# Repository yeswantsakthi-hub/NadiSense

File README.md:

# NadiSense — continuous-wear smart ring for overnight pulse-based screening

**Vishwakarma Awards 2026-27 · Frontier Diagnostics: The Next Vital Signs · Application ID VK26-AU-FD-0015**
Rajalakshmi Engineering College, Chennai · Team: Ring of Care · Faculty guide: Dr. L. Bhagyalakshmi, Professor, Dept. of ECE

NadiSense turns Nadi Pariksha — the traditional reading of the pulse's rate, rhythm, force and hardness — into
measurable photoplethysmography (PPG) features. A finger-worn ring records the pulse wave, SpO₂, skin temperature
and motion through the night and flags risk for:

- **AF-type irregular rhythm** (beat-to-beat interval variability)
- **Sleep-apnea risk** (overnight SpO₂ desaturation events)
- **Hypertension risk trends** (PPG stiffness index — Kathinya)
- **Baseline deviation** (heart rate, temperature)

It screens and refers to a clinician; it does not diagnose or report blood-pressure numbers.

## Repository layout

| Folder | Contents |
|---|---|
| `cad/` | Parametric ring model (`nadisense_ring.py`, CadQuery), full assembly `NadiSense_Ring_v2.step`, shell `Outer_shell.step`, one STL per part, render script |
| `fea/` | Linear-static FEA of the shell (`fea_squeeze.py`), results for three meshes (`fea_results.jsonl`), stress plot |
| `electronics/kicad/` | (Stage 2 submission, simplified) KiCad 7 project: wired schematic, project symbol library, ERC report (0 errors, 0 warnings), netlist, PDF and PNG of the sheet, generator script |
| `electronics/ring_v2_revB/` | **Rev B schematic + flex PCB**: manufacturer pin maps, routed 2-layer flex, DRC 0 errors / 0 unconnected, Gerbers, BOM, pick-and-place, renders |
| `electronics/` | Power budget (`power_budget.py` + results) |
| `renders/` | Assembled, half-section and exploded views |
| `docs/` | Design summary, Stage 2 deck PDF, FreeCAD and KiCad screenshots |
| `app/` | Companion app (React + Vite + Firebase), live at https://nadisense-app.vercel.app, runs on simulated sensor data until the ring is built |

## Key design numbers

| Item | Value | Source |
|---|---|---|
| Ring envelope | ID 19 mm, OD 26 mm, width 8 mm | `cad/nadisense_ring.py` |
| Battery | 12 mAh curved Li-Po (245 mm³ cavity) | CAD volume |
| Average current | 40 µA (night 98 µA, day 12 µA) | `electronics/power_budget.py` |
| Battery life | 9.9 days nominal, 6.0 days worst case | `electronics/power_budget.py` |
| Shell FEA, 50 N squeeze | Peak von Mises 8.5 MPa, deflection 0.12 mm, FoS 5.9 | `fea/fea_results.jsonl` |
| Mesh convergence | 9.35 → 8.53 → 8.46 MPa (0.8 % last step) | `fea/fea_results.jsonl` |
| Unit BOM (estimate) | ₹4,370 | `docs/design_summary.md` |

## Reproduce

```bash
pip install cadquery pyvista tetgen scikit-fem pyamg kiutils matplotlib
python cad/nadisense_ring.py cad/            # STEP + STL
python cad/render_pv.py cad/ renders/         # renders
python fea/fea_squeeze.py cad/ fea/ 0.08 0.5 pq2.0Q plot   # FEA (about 4 min, about 3 GB RAM)
python electronics/power_budget.py           # power budget
python electronics/kicad/kicad_gen.py electronics/kicad/   # KiCad schematic (needs KiCad 7 symbol libraries)
```

## Hardware

nRF52840 (BLE 5 SoC) · MAX86141 optical AFE with red 660 nm / IR 880 nm LEDs and Si photodiode · TMP117 (±0.1 °C) ·
LIS2DW12 accelerometer · BQ25120A charger with 2.2 µH buck inductor (3.3 V SYS) · 12 mAh Li-Po · biocompatible SLA resin shell with clear optical window.

Renders, the schematic image and the FEA plot were generated with AI assistance from these design files.

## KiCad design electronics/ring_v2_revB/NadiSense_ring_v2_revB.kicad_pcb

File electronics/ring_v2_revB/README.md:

# NadiSense ring v2 - schematic + flex PCB, Rev B

Rev B replaces the Stage 2 simplified schematic (`../kicad/`) and the Rev A layout study. Every IC now uses its
manufacturer pin / ball map and the support parts its data sheet calls for, and the flex PCB is routed against
those real footprints.

| Item | Rev B |
|---|---|
| Board | 66.8 x 6.0 mm strip, wraps 330 deg at r = 11.6 mm inside the ring; optics centred at 24.3 mm under the window |
| Stackup | 2-layer polyimide flex: 25 um PI, 12 um Cu + plating, 25 um coverlay both sides, ENIG, ~0.11 mm |
| Vias | 77 laser vias 0.2/0.1 mm in the BGA pads (filled + capped, VIPPO); 265 routing / ground-stitching vias 0.35/0.15 mm |
| Rules | 75 um track / 75 um space, 0.15 mm copper-to-edge, 0.2 mm hole-to-hole |
| Pours | GND top (solid); bottom solid under the stiffened IC sections, cross-hatched in the bend sections |
| Parts | 43 on the top (finger) side, 6 test pads on the bottom; 49 total, 37 nets |
| Checks | KiCad 7.0.11 DRC **0 violations, 0 unconnected** (`DRC.rpt`); board pads vs schematic **0 mismatches** (`verify_pcb.py`); schematic netlist vs design **0 problems** (`verify_net.py`) |

## Power architecture (changed from Stage 2)

The BQ25120A buck output (SYS) is the single **1.8 V rail** for every IC. The nRF52840 runs in normal-voltage
mode (VDD = VDDH = 1.8 V, internal LDOs), so no 3.3 V rail is needed. The LEDs run from VBAT through the
MAX86141 drivers. The Stage 2 deck and report describe a 3.3 V buck feeding the nRF52840 regulator; Rev B
simplifies this.

## Parts and pin maps

| Ref | Part | Package / footprint | Pin-map source |
|---|---|---|---|
| U1 | nRF52840-CKAA | WLCSP-94, 0.35 mm pitch | Nordic nRF52840 PS, "Pin assignments - WLCSP" |
| U2 | MAX86141ENP+ | WLP-20 (5 x 4), 0.4 mm | ADI MAX86140/86141 data sheet, bump configuration |
| U3 | TMP117AIDRVR | WSON-6 2 x 2 mm + pad | TI TMP117 data sheet, pin functions |
| U4 | LIS2DW12TR | LGA-12 2 x 2 mm | ST LIS2DW12 data sheet, pin description |
| U5 | BQ25120AYFPR | DSBGA-25 (5 x 5), 0.5 mm | TI BQ25120A data sheet, pin configuration |

nRF52840 signal map: SPI SCK C10 (P0.04), MOSI D10 (P0.05), MISO E10 (P0.08), AFE_CS F10 (P1.09), AFE_INT G10
(P0.12); I2C SDA B10 (P0.01), SCL K7 (P0.15); ACC_INT A6 (P0.28), TEMP_ALRT K3 (P0.22), CHG_INT K2 (P0.25),
CHG_CD A7 (P0.30); nRESET K6; SWD J2/H2. Unused P0.29 (C7) is tied to GND to link the fenced-in VSS ball B7.
I2C addresses: TMP117 0x48, LIS2DW12 0x18, BQ25120A 0x6A.

## Layout, left to right

Chip antenna AE1 (copper keep-out) - pi-match C8/L2/C9 and 32 MHz crystal Y1 - nRF52840 U1 with decoupling -
LIS2DW12 U4 + I2C pull-ups - red LED D1, photodiode D3, IR LED D2 (optical window) - MAX86141 U2 - TMP117 U3 -
BQ25120A U5 with L1 and its capacitors / set resistors - charge pads J1 - Li-Po tabs BT1 - free strip behind the cell.
Bottom side: programming pads TP1 SWDIO, TP2 SWDCLK, TP3 nRESET, TP4 +1V8, TP5 GND next to the SoC (needs a
cut-out in the stiffener) and TP6 MR by the charger.

## Files

| File | What it is |
|---|---|
| `NadiSense_ring_v2_revB.kicad_sch` / `.kicad_pcb` / `.kicad_pro` | KiCad 7 project (open the `.kicad_pro`) |
| `NadiSense.kicad_sym`, `NadiSense.pretty/` | project symbols and footprints (IC land patterns, test pads, contacts) |
| `NadiSense_ring_v2_revB_schematic.pdf` | schematic |
| `NadiSense_ring_v2_revB_top.pdf`, `_bottom.pdf` | layer plots with the board outline and stiffeners |
| `NadiSense_ring_v2_revB_gerbers.zip`, `fab/` | Gerbers, Excellon drill + maps, pick-and-place, BOM |
| `images/` | overview, 3D flat + ring renders, routing view, assembly drawings, layer views |
| `DRC.rpt` | final design-rule check |
| `design.py` | single source of truth: parts, values, footprints, pin maps, nets |

## How the board was built

1. `build_sch.py` writes the schematic from `design.py`; `kicad-cli sch export netlist`; `verify_net.py` checks it.
2. `build_pcb.py` writes the footprints, outline, rules, rule areas, placement and via-in-pad fan-out, and a Specctra DSN.
3. Freerouting 1.9.0 routes the DSN (`-mp 120`); `route_import.py --no-pour` imports the session.
4. `finish2.py` (two-layer A* router) completes nets the autorouter left open; autorouted GND tracks are removed
   because the pours carry ground.
5. `finalize.py` adds the pours and stitching vias; `gnd_ties.py` and `gnd_bridge.py` tie the inner BGA ground and
   any isolated pour island into the main ground; `setrules.py` keeps the flex rules in the project file.
6. `drc.py`, `verify_pcb.py` for the checks; `make_outputs.py`, `drawings.py`, `render3d.py` for the deliverables.

## Before fabrication (open items)

1. **Land patterns to confirm against the package drawings:** U1 against Nordic PS section 7.2.3 (0.35 mm pitch
   derived from the 3.544 x 3.607 mm body and 10 x 10 grid), U2 against ADI outline 21-100134 / AN1891, U4 pad-1
   orientation against ST's land pattern.
2. **Fab capability:** 0.35 mm-pitch WLCSP on flex needs laser via-in-pad (filled, capped) and 75 um lines; confirm
   with the flex vendor, or move to a 4-layer flex if they prefer.
3. **Values still to set:** R4 (ISET) and R5 (IPRETERM) per TI's equations (charge current is also set over I2C);
   C8/L2/C9 antenna match to be tuned on a VNA in the potted ring; nRF52840 decoupling values (C1 DEC1 100 nF, C2
   DEC4 1 uF, C3 DEC6 47 nF, C4/C5 VDD) to be checked against Nordic's CKAA reference circuit.
4. **Antenna:** it sits next to the cell end; check range in the finished ring.
5. **Not yet done:** signal-integrity/RF simulation, thermal check of the LED drive, and a review in the KiCad GUI.

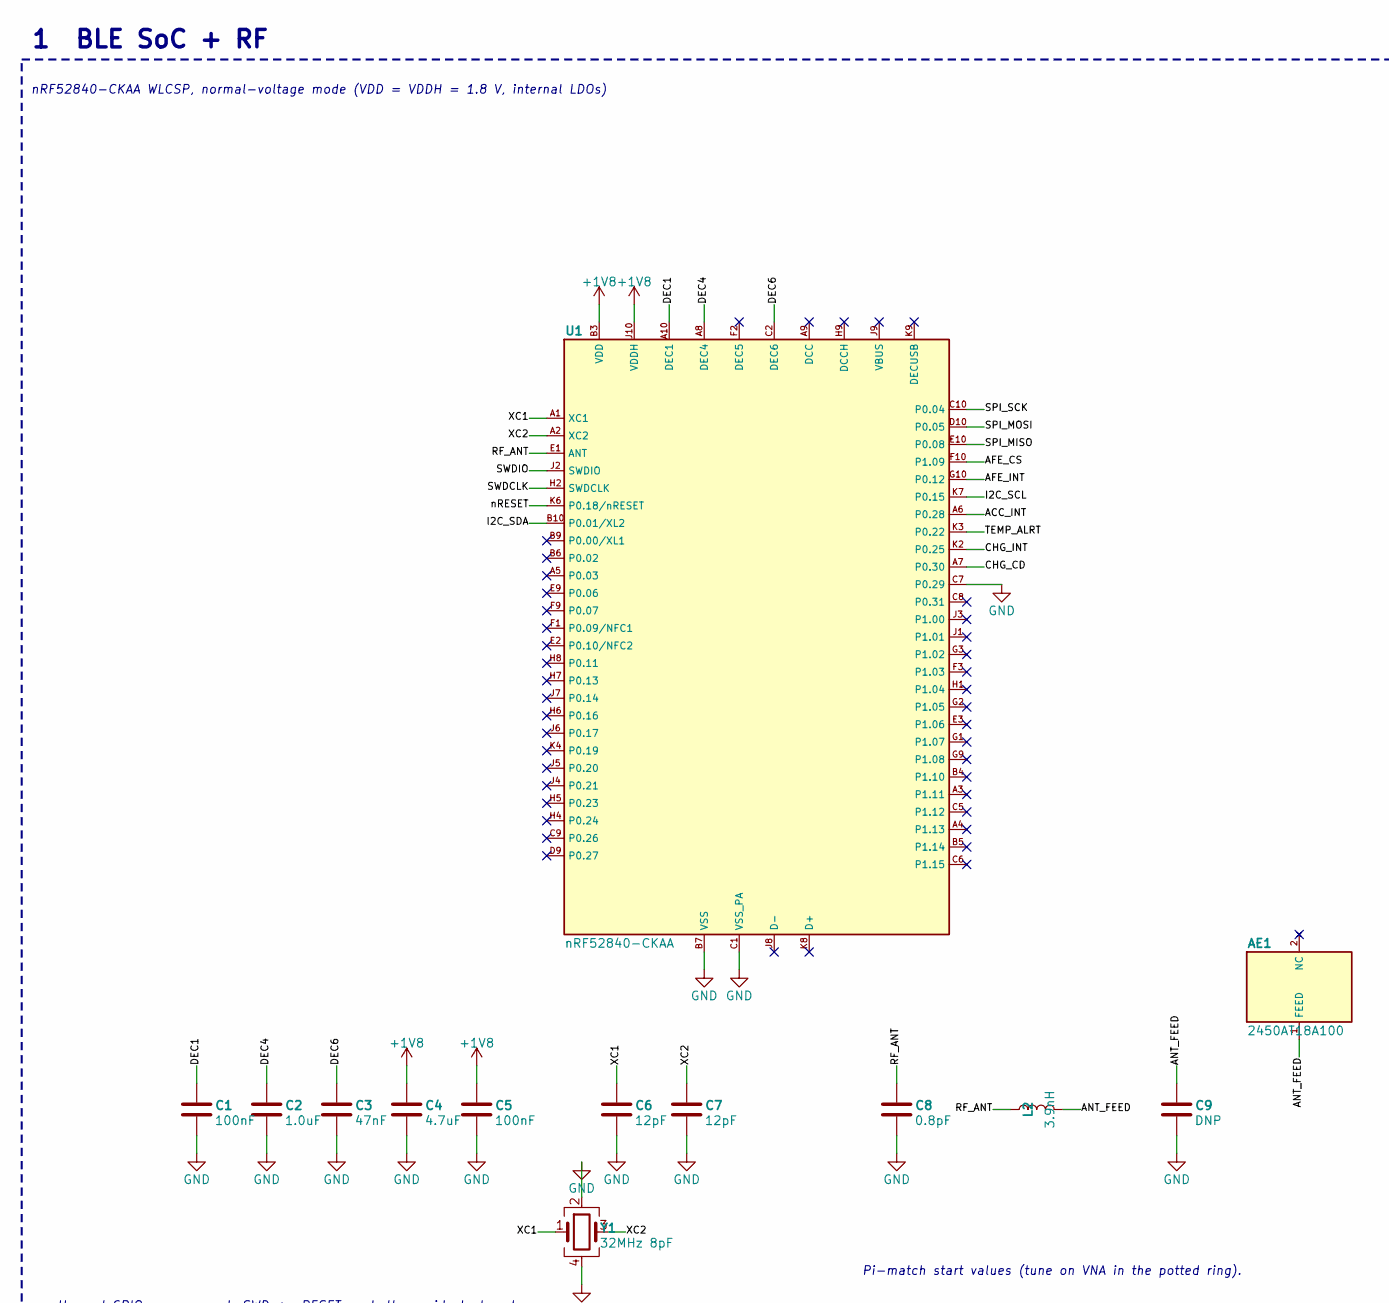
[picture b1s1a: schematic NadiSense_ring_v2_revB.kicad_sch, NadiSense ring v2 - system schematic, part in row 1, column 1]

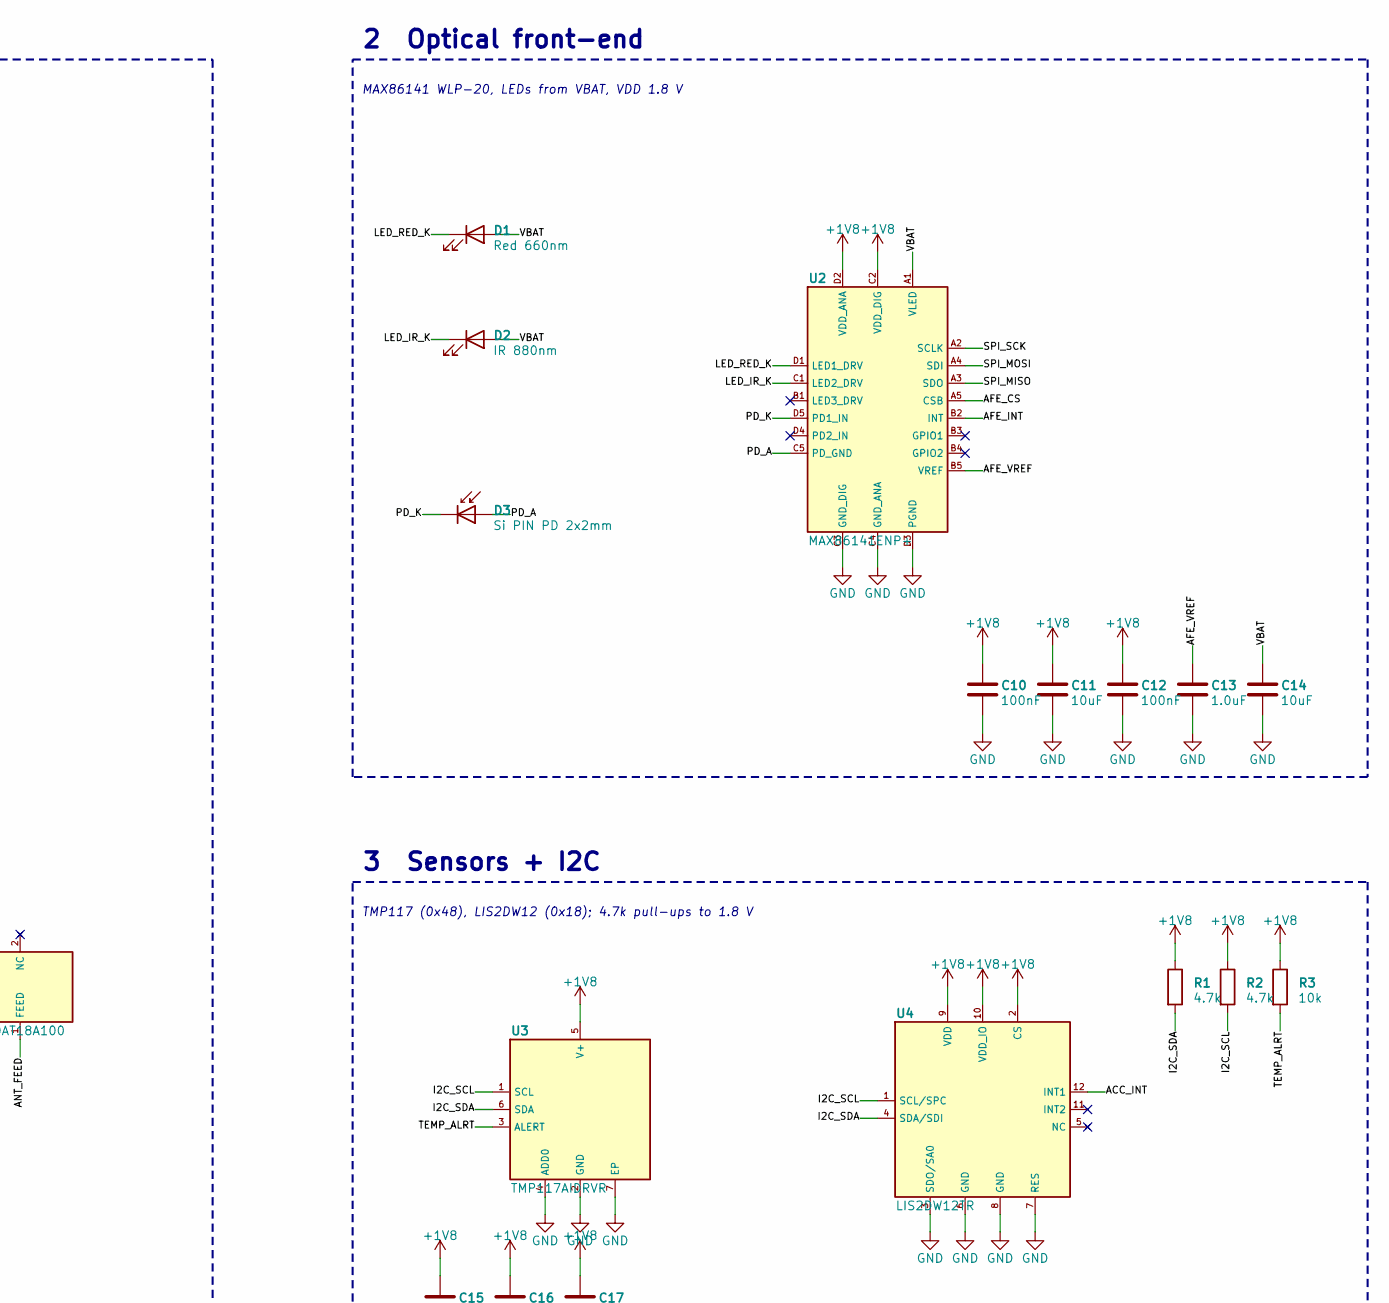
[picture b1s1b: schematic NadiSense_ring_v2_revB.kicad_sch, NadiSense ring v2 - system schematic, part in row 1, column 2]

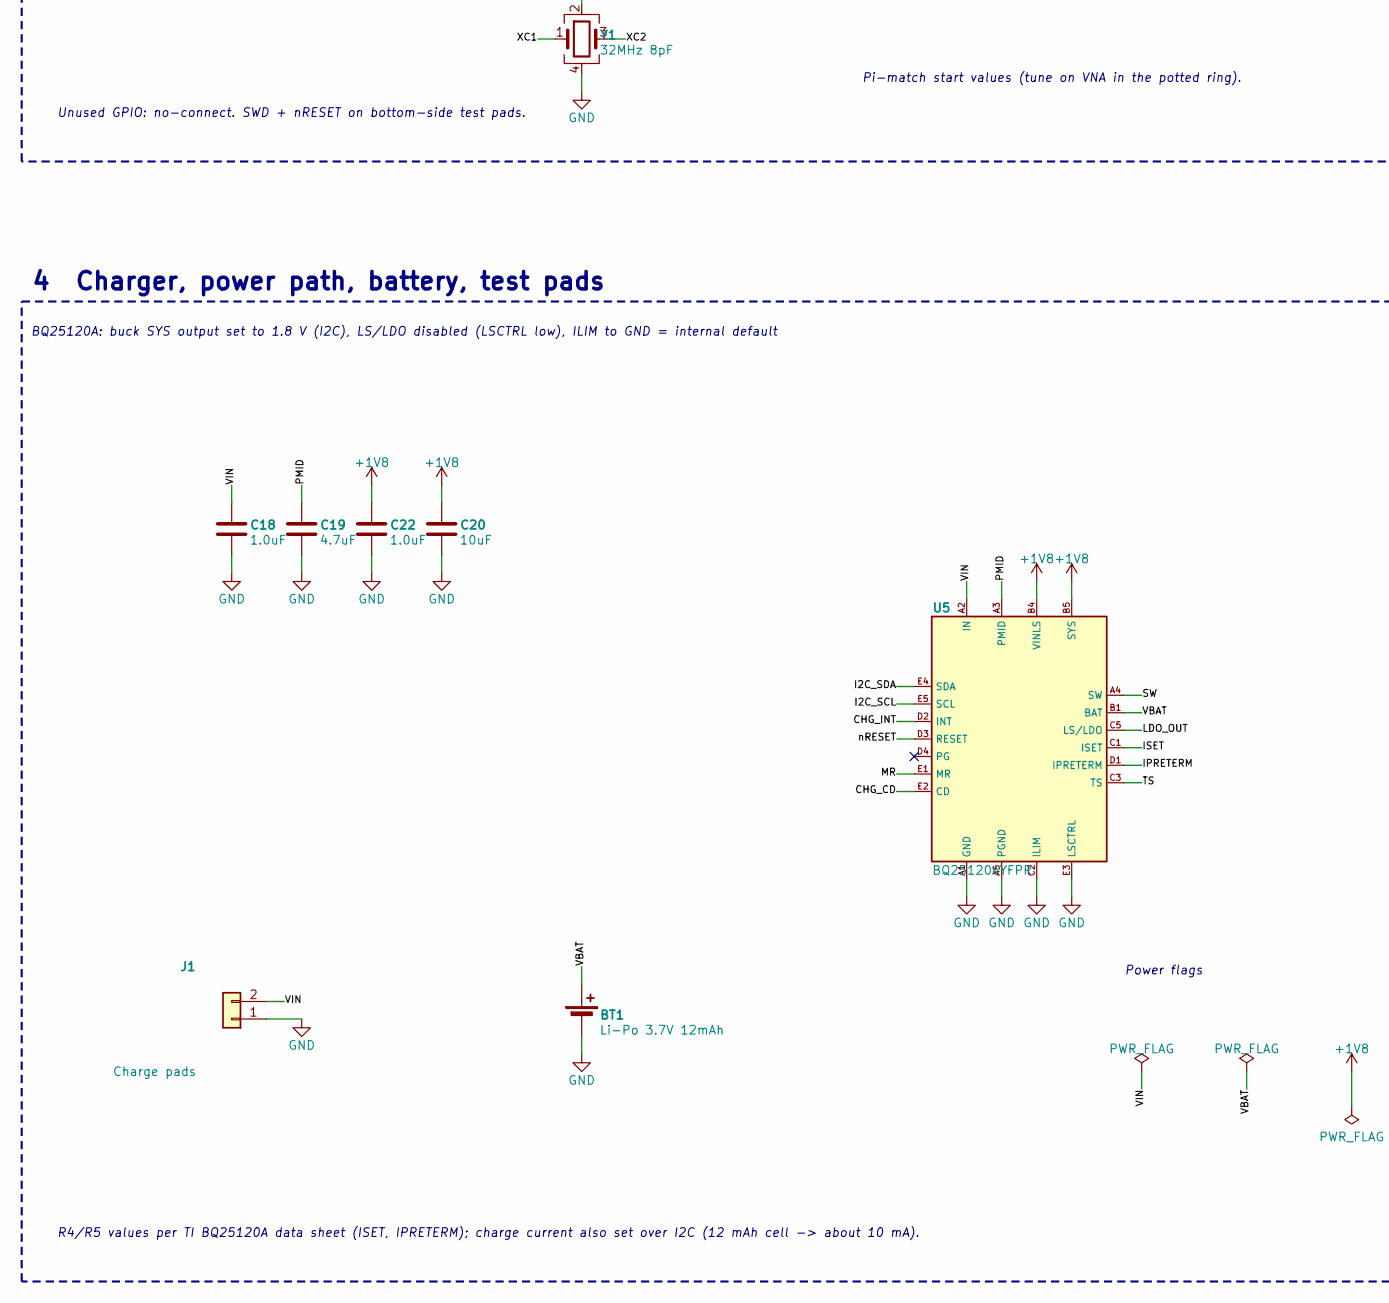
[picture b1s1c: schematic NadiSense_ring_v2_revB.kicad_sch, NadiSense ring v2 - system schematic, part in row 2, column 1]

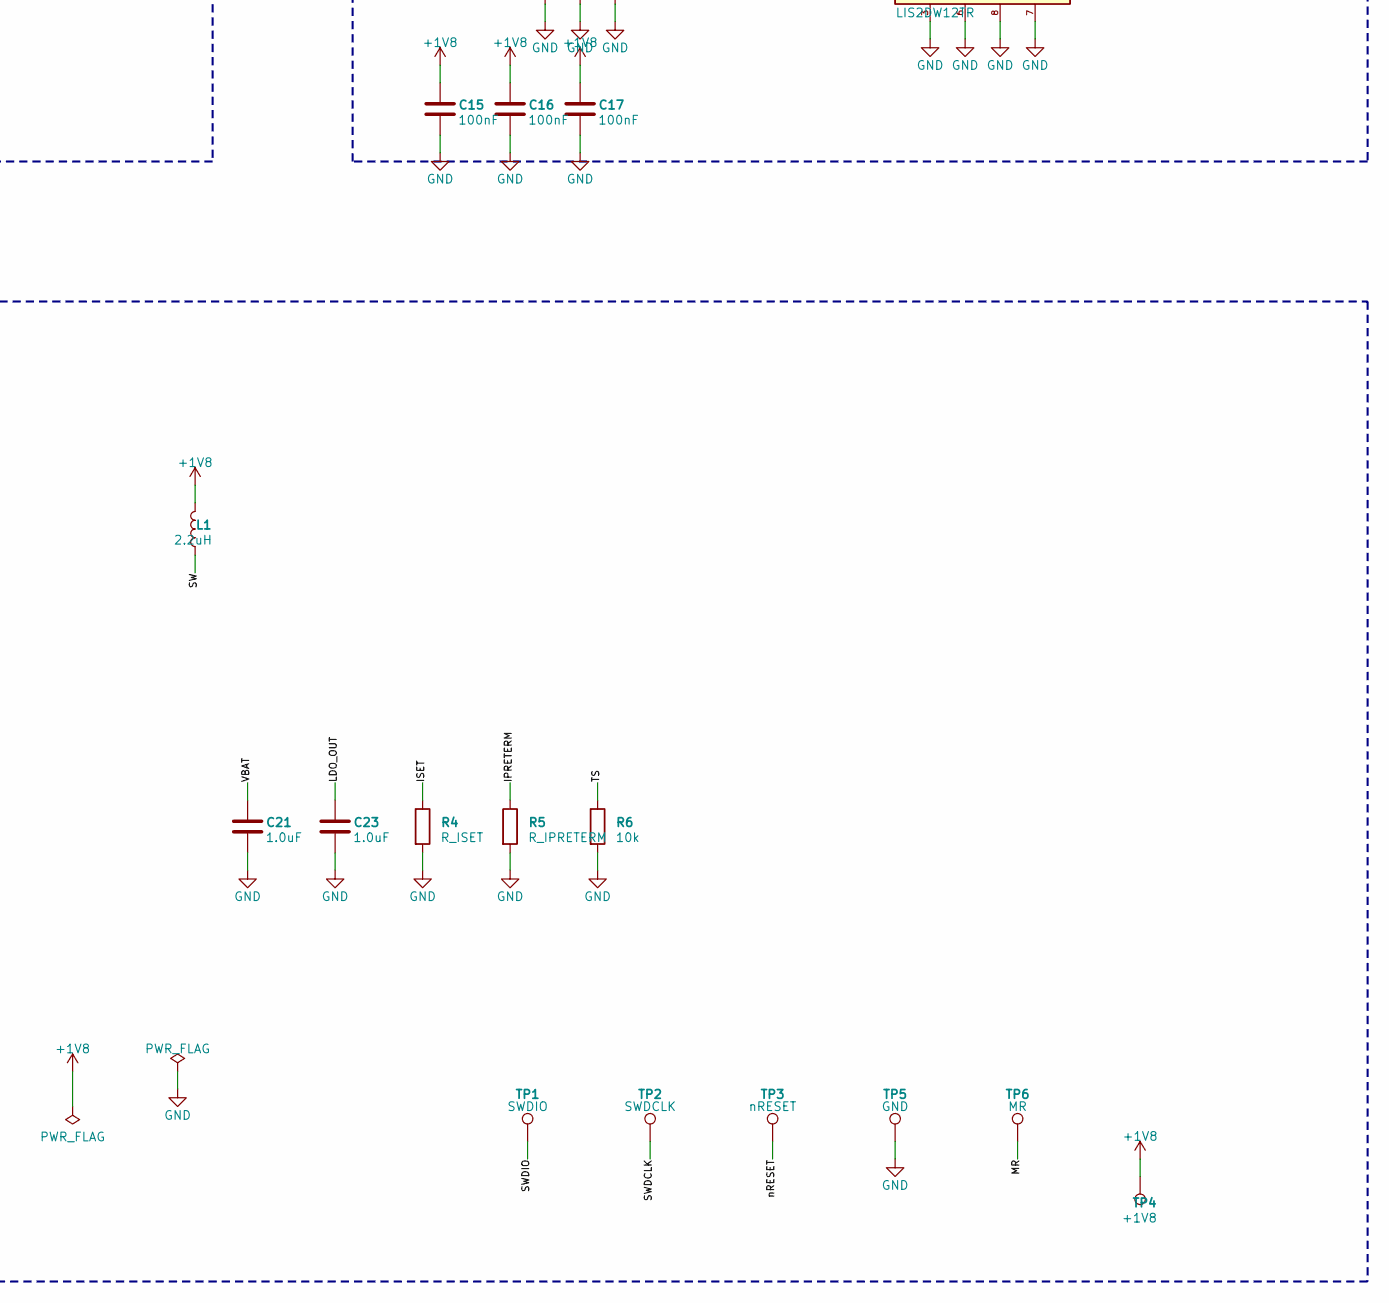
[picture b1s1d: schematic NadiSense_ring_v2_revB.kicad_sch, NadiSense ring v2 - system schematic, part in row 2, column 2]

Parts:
AE1: 2450AT18A100; Johanson_2450AT18x100
BT1: Li-Po 3.7V 12mAh; LiPo_Tabs_1.6x1.9mm
C1, C5, C10, C12, C15, C16, C17: 100nF; C_0201_0603Metric
C2, C18, C21: 1.0uF; C_0402_1005Metric
C3: 47nF; C_0201_0603Metric
C4, C19: 4.7uF; C_0402_1005Metric
C6, C7: 12pF; C_0201_0603Metric
C8: 0.8pF; C_0201_0603Metric
C9: DNP; C_0201_0603Metric
C11, C14, C20: 10uF; C_0402_1005Metric
C13, C22, C23: 1.0uF; C_0201_0603Metric
D1: Red 660nm; LED_0603_1608Metric
D2: IR 880nm; LED_0603_1608Metric
D3: Si PIN PD 2x2mm; PD_2x2mm
J1: Charge pads; ChargePads_2xD1.2mm
L1: 2.2uH; L_0603_1608Metric
L2: 3.9nH; L_0201_0603Metric
R1, R2: 4.7k; R_0201_0603Metric
R3, R6: 10k; R_0201_0603Metric
R4: R_ISET; R_0201_0603Metric
R5: R_IPRETERM; R_0201_0603Metric
TP1: SWDIO; TestPad_D0.8mm
TP2: SWDCLK; TestPad_D0.8mm
TP3: nRESET; TestPad_D0.8mm
TP4: +1V8; TestPad_D0.8mm
TP5: GND; TestPad_D0.8mm
TP6: MR; TestPad_D0.8mm
U1: nRF52840-CKAA; Nordic_WLCSP-94_3.544x3.607mm_P0.35mm
U2: MAX86141ENP+; Maxim_WLP-20_2.048x1.848mm_Layout5x4_P0.4mm
U3: TMP117AIDRVR; WSON-6-1EP_2x2mm_P0.65mm_EP1x1.6mm
U4: LIS2DW12TR; LGA-12_2x2mm_P0.5mm
U5: BQ25120AYFPR; TI_DSBGA-25_2.5x2.5mm_Layout5x5_P0.5mm
Y1: 32MHz 8pF; Crystal_SMD_2016-4Pin_2.0x1.6mm

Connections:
+1V8: C4.1, C5.1, C10.1, C11.1, C12.1, C15.1, C16.1, C17.1, C20.1, C22.1, L1.2, R1.1, R2.1, R3.1, TP4.1, U1.B3 (VDD), U1.B8 (VDD), U1.H10 (VDD), U1.J10 (VDDH), U1.K1 (VDD), U1.K5 (VDD), U2.C2 (VDD_DIG), U2.D2 (VDD_ANA), U3.5 (V+), U4.2 (CS), U4.9 (VDD), U4.10 (VDD_IO), U5.B4 (VINLS), U5.B5 (SYS), U5.C4 (VINLS)
/ACC_INT: U1.A6 (P0.28), U4.12 (INT1)
/AFE_CS: U1.F10 (P1.09), U2.A5 (CSB)
/AFE_INT: U1.G10 (P0.12), U2.B2 (INT)
/AFE_VREF: C13.1, U2.B5 (VREF)
/ANT_FEED: AE1.1 (FEED), C9.1, L2.2
/CHG_CD: U1.A7 (P0.30), U5.E2 (CD)
/CHG_INT: U1.K2 (P0.25), U5.D2 (INT)
/DEC1: C1.1, U1.A10 (DEC1)
/DEC4: C2.1, U1.A8 (DEC4)
/DEC6: C3.1, U1.C2 (DEC6)
/I2C_SCL: R2.2, U1.K7 (P0.15), U3.1 (SCL), U4.1 (SCL/SPC), U5.E5 (SCL)
/I2C_SDA: R1.2, U1.B10 (P0.01/XL2), U3.6 (SDA), U4.4 (SDA/SDI), U5.E4 (SDA)
/IPRETERM: R5.1, U5.D1 (IPRETERM)
/ISET: R4.1, U5.C1 (ISET)
/LDO_OUT: C23.1, U5.C5 (LS/LDO)
/LED_IR_K: D2.1 (K), U2.C1 (LED2_DRV)
/LED_RED_K: D1.1 (K), U2.D1 (LED1_DRV)
/MR: TP6.1, U5.E1 (MR)
/PD_A: D3.2 (A), U2.C5 (PD_GND)
/PD_K: D3.1 (K), U2.D5 (PD1_IN)
/PMID: C19.1, U5.A3 (PMID), U5.B3 (PMID)
/RF_ANT: C8.1, L2.1, U1.E1 (ANT)
/SPI_MISO: U1.E10 (P0.08), U2.A3 (SDO)
/SPI_MOSI: U1.D10 (P0.05), U2.A4 (SDI)
/SPI_SCK: U1.C10 (P0.04), U2.A2 (SCLK)
/SW: L1.1, U5.A4 (SW)
/SWDCLK: TP2.1, U1.H2 (SWDCLK)
/SWDIO: TP1.1, U1.J2 (SWDIO)
/TEMP_ALRT: R3.2, U1.K3 (P0.22), U3.3 (ALERT)
/TS: R6.1, U5.C3 (TS)
/VBAT: BT1.1 (+), C14.1, C21.1, D1.2 (A), D2.2 (A), U2.A1 (VLED), U5.B1 (BAT), U5.B2 (BAT)
/VIN: C18.1, J1.2, U5.A2 (IN)
/XC1: C6.1, U1.A1 (XC1), Y1.1
/XC2: C7.1, U1.A2 (XC2), Y1.3
/nRESET: TP3.1, U1.K6 (P0.18/nRESET), U5.D3 (RESET)
GND: BT1.2 (-), C1.2, C2.2, C3.2, C4.2, C5.2, C6.2, C7.2, C8.2, C9.2, C10.2, C11.2, C12.2, C13.2, C14.2, C15.2, C16.2, C17.2, C18.2, C19.2, C20.2, C21.2, C22.2, C23.2, J1.1, R4.2, R5.2, R6.2, TP5.1, U1.B7 (VSS), U1.C1 (VSS_PA), U1.C4 (VSS), U1.C7 (P0.29), U1.D3 (VSS), U1.D4 (VSS), U1.D5 (VSS), U1.D6 (VSS), U1.D7 (VSS), U1.D8 (VSS), U1.E4 (VSS), U1.E5 (VSS), U1.E6 (VSS), U1.E7 (VSS), U1.E8 (VSS), U1.F4 (VSS), U1.F5 (VSS), U1.F6 (VSS), U1.F7 (VSS), U1.F8 (VSS), U1.G4 (VSS), U1.G5 (VSS), U1.G6 (VSS), U1.G7 (VSS), U1.G8 (VSS), U1.K10 (VSS), U2.C3 (GND_DIG), U2.C4 (GND_ANA), U2.D3 (PGND), U3.2 (GND), U3.4 (ADD0), U3.7 (EP), U4.3 (SDO/SA0), U4.6 (GND), U4.7 (RES), U4.8 (GND), U5.A1 (GND), U5.A5 (PGND), U5.C2 (ILIM), U5.D5 (GND), U5.E3 (LSCTRL), Y1.2, Y1.4

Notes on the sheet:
1 BLE SoC + RF
nRF52840-CKAA WLCSP, normal-voltage mode (VDD = VDDH = 1.8 V, internal LDOs)
Pi-match start values (tune on VNA in the potted ring).
Unused GPIO: no-connect. SWD + nRESET on bottom-side test pads.
2 Optical front-end
MAX86141 WLP-20, LEDs from VBAT, VDD 1.8 V
3 Sensors + I2C
TMP117 (0x48), LIS2DW12 (0x18); 4.7k pull-ups to 1.8 V
4 Charger, power path, battery, test pads
BQ25120A: buck SYS output set to 1.8 V (I2C), LS/LDO disabled (LSCTRL low), ILIM to GND = internal default
R4/R5 values per TI BQ25120A data sheet (ISET, IPRETERM); charge current also set over I2C (12 mAh cell -> about 10 mA).
Power flags

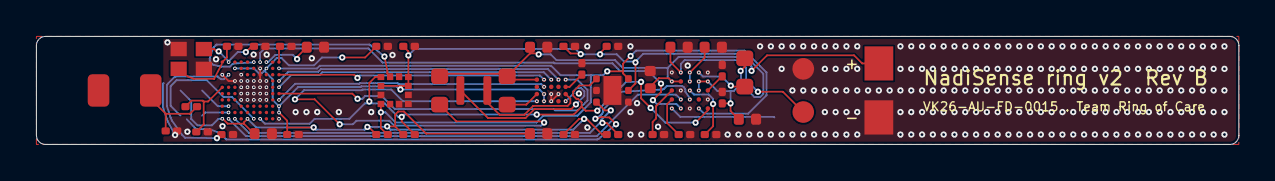
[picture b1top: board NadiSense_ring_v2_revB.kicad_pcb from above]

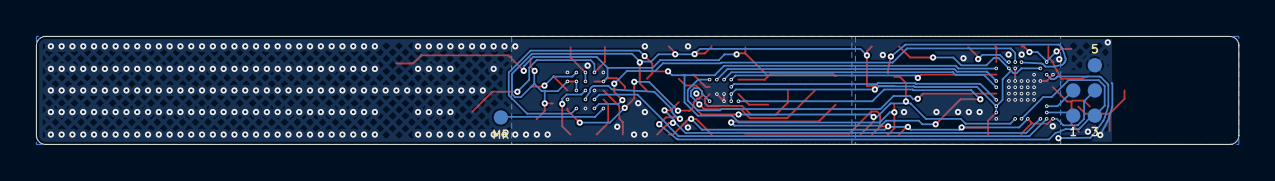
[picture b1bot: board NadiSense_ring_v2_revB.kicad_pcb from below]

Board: 2 copper layers, 66.8 x 6.0 mm, 49 parts (6 on the bottom side), 37 nets.

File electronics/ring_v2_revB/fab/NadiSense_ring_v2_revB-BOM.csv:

Qty,References,Value,Footprint,Side,Note
1,AE1,2450AT18A100,RF_Antenna:Johanson_2450AT18x100,Top,
1,BT1,Li-Po 3.7V 12mAh,NadiSense:LiPo_Tabs_1.6x1.9mm,Top,
7,C1 C5 C10 C12 C15 C16 C17,100nF,Capacitor_SMD:C_0201_0603Metric,Top,
3,C2 C18 C21,1.0uF,Capacitor_SMD:C_0402_1005Metric,Top,
1,C3,47nF,Capacitor_SMD:C_0201_0603Metric,Top,
2,C4 C19,4.7uF,Capacitor_SMD:C_0402_1005Metric,Top,
2,C6 C7,12pF,Capacitor_SMD:C_0201_0603Metric,Top,
1,C8,0.8pF,Capacitor_SMD:C_0201_0603Metric,Top,C8: RF pi-match start value - tune with a VNA in the finished ring
0,C9,DNP,Capacitor_SMD:C_0201_0603Metric,Top,
3,C11 C14 C20,10uF,Capacitor_SMD:C_0402_1005Metric,Top,
3,C13 C22 C23,1.0uF,Capacitor_SMD:C_0201_0603Metric,Top,
1,D1,Red 660nm,LED_SMD:LED_0603_1608Metric,Top,
1,D2,IR 880nm,LED_SMD:LED_0603_1608Metric,Top,
1,D3,Si PIN PD 2x2mm,NadiSense:PD_2x2mm,Top,
1,J1,Charge pads,NadiSense:ChargePads_2xD1.2mm,Top,
1,L1,2.2uH,Inductor_SMD:L_0603_1608Metric,Top,
1,L2,3.9nH,Inductor_SMD:L_0201_0603Metric,Top,L2: RF pi-match start value - tune with a VNA in the finished ring
2,R1 R2,4.7k,Resistor_SMD:R_0201_0603Metric,Top,
2,R3 R6,10k,Resistor_SMD:R_0201_0603Metric,Top,R6: TS: 10k emulates a 10k NTC at 25 C (cell has no NTC); TS can be disabled over I2C
1,R4,R_ISET,Resistor_SMD:R_0201_0603Metric,Top,"R4: fast-charge current set resistor; value per TI BQ25120A data sheet (ISET), charge current is also set over I2C"
1,R5,R_IPRETERM,Resistor_SMD:R_0201_0603Metric,Top,R5: pre-charge/termination resistor; value per TI data sheet (IPRETERM)
1,TP1,SWDIO,NadiSense:TestPad_D0.8mm,Bottom,
1,TP2,SWDCLK,NadiSense:TestPad_D0.8mm,Bottom,
1,TP3,nRESET,NadiSense:TestPad_D0.8mm,Bottom,
1,TP4,+1V8,NadiSense:TestPad_D0.8mm,Bottom,
1,TP5,GND,NadiSense:TestPad_D0.8mm,Bottom,
1,TP6,MR,NadiSense:TestPad_D0.8mm,Bottom,
1,U1,nRF52840-CKAA,NadiSense:Nordic_WLCSP-94_3.544x3.607mm_P0.35mm,Top,
1,U2,MAX86141ENP+,NadiSense:Maxim_WLP-20_2.048x1.848mm_Layout5x4_P0.4mm,Top,
1,U3,TMP117AIDRVR,Package_SON:WSON-6-1EP_2x2mm_P0.65mm_EP1x1.6mm,Top,
1,U4,LIS2DW12TR,Package_LGA:LGA-12_2x2mm_P0.5mm,Top,
1,U5,BQ25120AYFPR,NadiSense:TI_DSBGA-25_2.5x2.5mm_Layout5x5_P0.5mm,Top,
1,Y1,32MHz 8pF,Crystal:Crystal_SMD_2016-4Pin_2.0x1.6mm,Top,

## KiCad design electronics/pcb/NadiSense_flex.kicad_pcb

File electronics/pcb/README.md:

# NadiSense ring v2 flex PCB, Rev A (layout study)

| Item | Value |
|---|---|
| Board | 66.8 x 6.0 mm strip, wraps 330 deg at r = 11.6 mm inside the ring |
| Stackup | 2-layer polyimide flex: 25 um PI, 1/3 oz Cu, 25 um coverlay both sides, ENIG, ~0.11 mm |
| Stiffeners | 0.1 mm FR4/PI under the IC sections (outlines on User.1); bends only in the free sections, min radius 10 mm |
| Rules | 75 um track/space minimum, default 0.1 mm tracks, 0.4/0.2 mm vias, 0.15 mm copper-to-edge |
| Parts | 26, all on the top side (faces the finger); optics centred at 24.3 mm, under the optical window |
| Routing | 333 track segments, 44 vias, Freerouting 1.9.0; GND pour on top (solid) and bottom (cross-hatched for flexibility) |
| Antenna | Johanson 2450AT18A100 at the strip end, no copper pour under or beyond it |
| DRC (KiCad 7.0.11) | **0 violations, 0 unconnected pads** (`DRC.rpt`) |

## Files

- `NadiSense_flex.kicad_pcb` / `.kicad_pro` / `fp-lib-table` - KiCad 7 board
- `NadiSense.pretty/` - project footprints (ICs, photodiode, crystal, charge pads, battery tabs)
- `NadiSense_flex_gerbers.zip`, `fab/` - Gerbers, Excellon drill + maps, pick-and-place, BOM
- `NadiSense_flex_top.pdf`, `NadiSense_flex_bottom.pdf` - layer plots
- `pcb_gen.py`, `route_import.py`, `drc.py`, `run_all.sh` - the scripts that build, route and check the board

## Layout, left to right

Chip antenna (3.4 mm) - nRF52840 (9.6) - 32 MHz crystal (13.3, moved next to the SoC; the CAD renders still show
it further along) - LIS2DW12 (16.2) - BQ25120A + 2.2 uH inductor (18.8, 20.9) - red LED, photodiode, IR LED
(22.4, 24.3, 26.15) - MAX86141 (28.6) - TMP117 (32.0) - charge pads (38.9) - Li-Po tabs (46.8) - free section
behind the cell.

## Before fabrication (open items)

1. **IC land patterns are simplified.** U1-U5 use the simplified schematic pin numbers on a 0.5 mm grid inside the
   real package outlines. Replace them with the manufacturer land patterns (nRF52840 WLCSP needs 0.35 mm-pitch
   via-in-pad / HDI flex), give the symbols the real ball map, and re-route.
2. Add the nRF52840 RF matching network and tune the antenna feed once the ring is potted.
3. Confirm stiffener, coverlay openings and bend zones with the flex fab.
4. Electrical check after re-route: ERC on the updated schematic, then DRC with the fab's rule file.

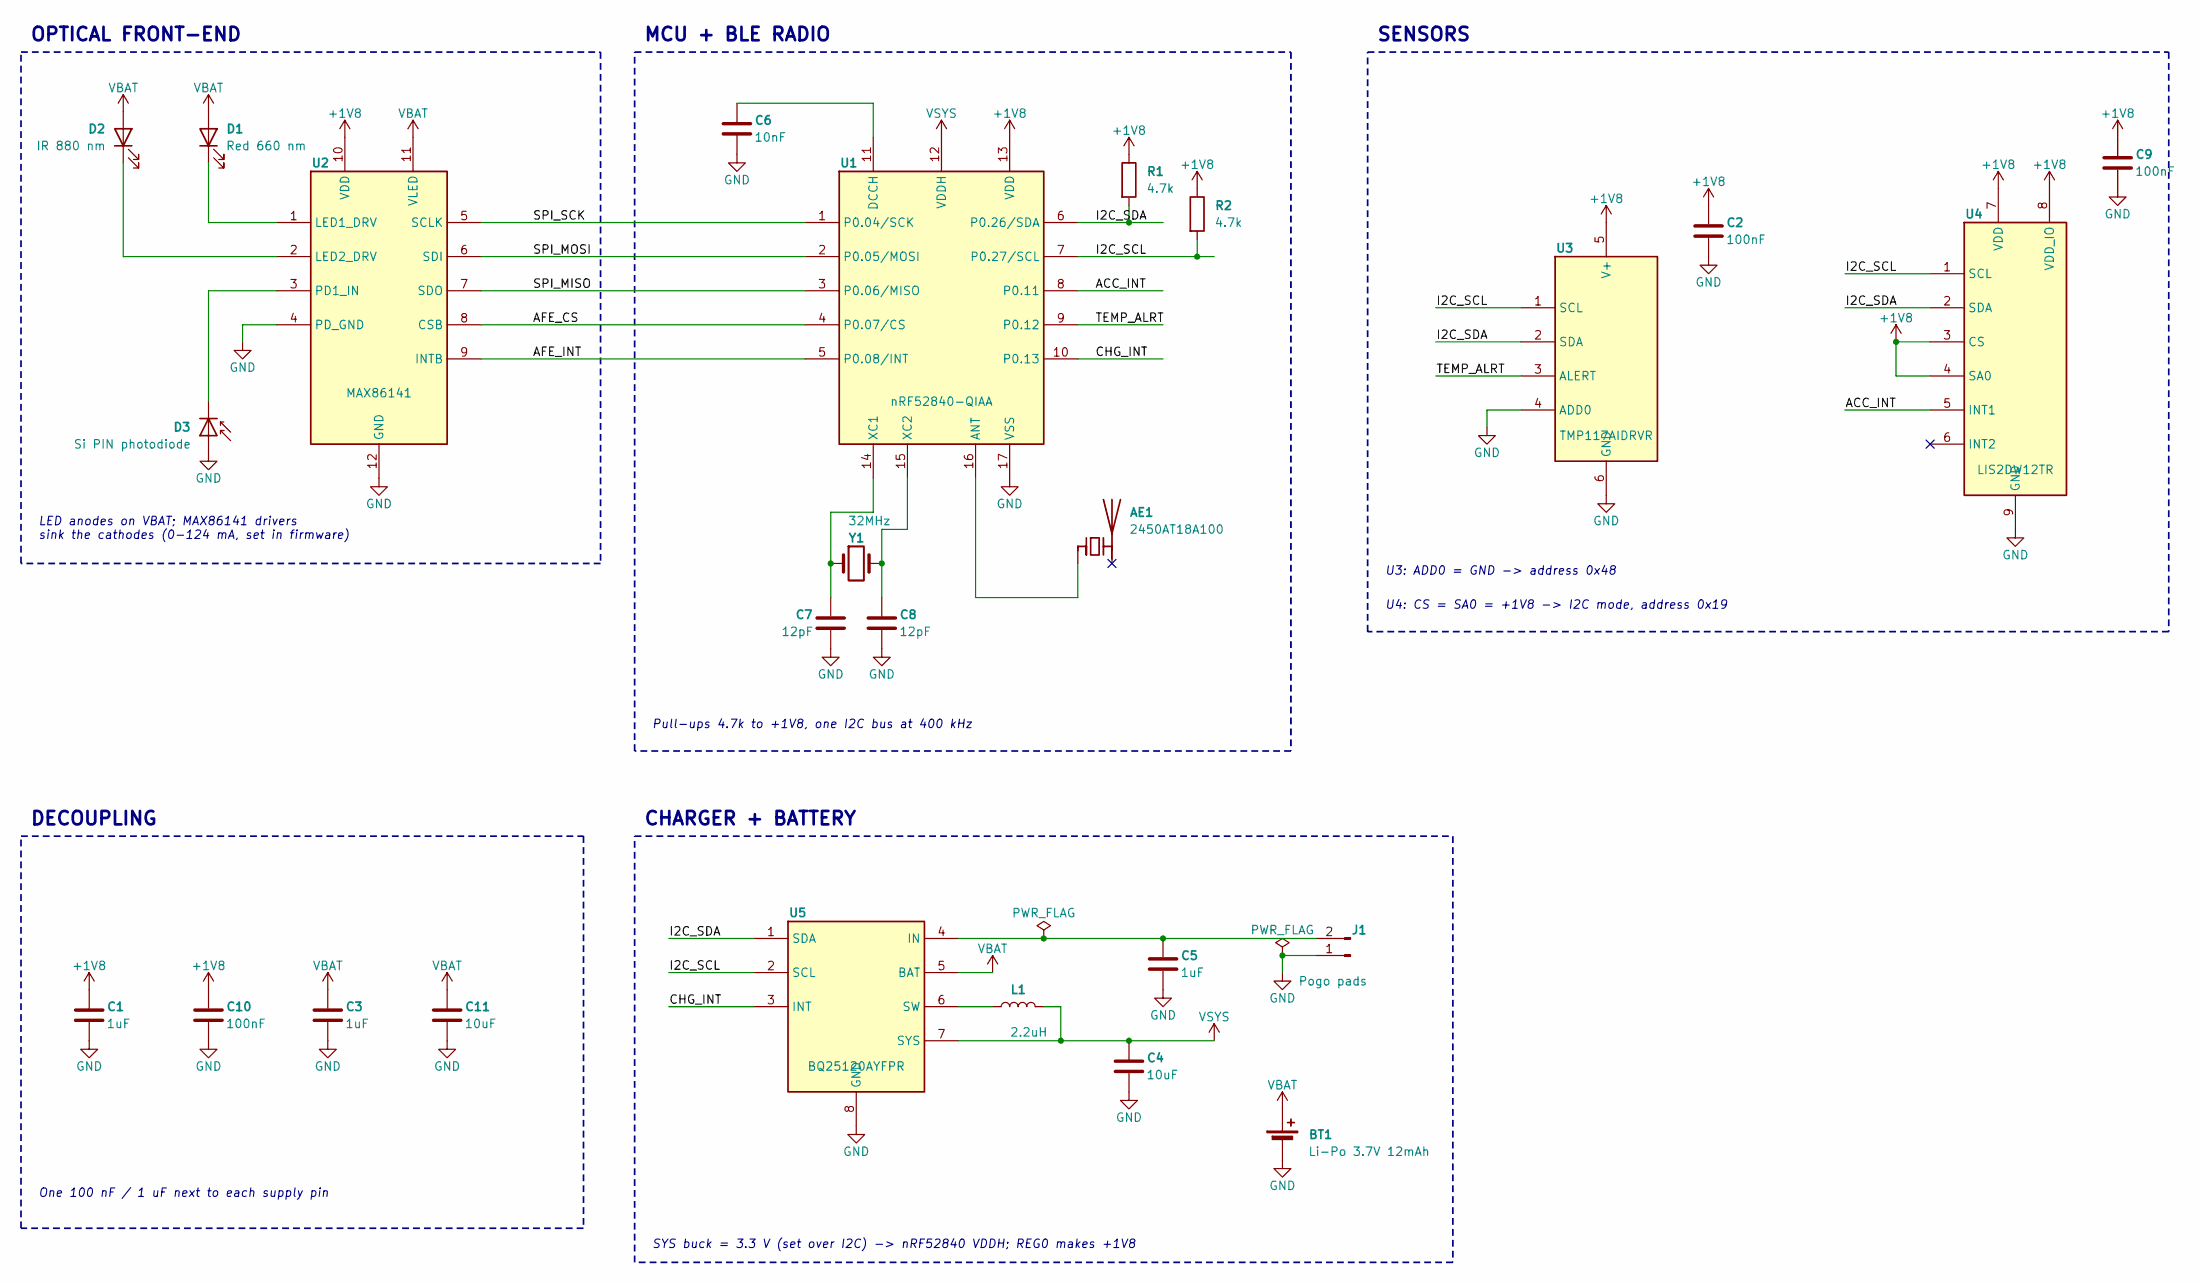
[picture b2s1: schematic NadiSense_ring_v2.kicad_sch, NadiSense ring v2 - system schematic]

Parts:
AE1: 2450AT18A100
BT1: Li-Po 3.7V 12mAh
C1, C3, C5: 1uF
C2, C9, C10: 100nF
C4, C11: 10uF
C6: 10nF
C7, C8: 12pF
D1: Red 660 nm
D2: IR 880 nm
D3: Si PIN photodiode
J1: Pogo pads
L1: 2.2uH
R1, R2: 4.7k
U1: nRF52840-QIAA
U2: MAX86141
U3: TMP117AIDRVR
U4: LIS2DW12TR
U5: BQ25120AYFPR
Y1: 32MHz

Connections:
+1V8: C1.1, C2.1, C9.1, C10.1, R1.1, R2.1, U1.13 (VDD), U2.10 (VDD), U3.5 (V+), U4.3 (CS), U4.4 (SA0), U4.7 (VDD), U4.8 (VDD_IO)
/ACC_INT: U1.8 (P0.11), U4.5 (INT1)
/AFE_CS: U1.4 (P0.07/CS), U2.8 (CSB)
/AFE_INT: U1.5 (P0.08/INT), U2.9 (INTB)
/CHG_INT: U1.10 (P0.13), U5.3 (INT)
/I2C_SCL: R2.2, U1.7 (P0.27/SCL), U3.1 (SCL), U4.1 (SCL), U5.2 (SCL)
/I2C_SDA: R1.2, U1.6 (P0.26/SDA), U3.2 (SDA), U4.2 (SDA), U5.1 (SDA)
/SPI_MISO: U1.3 (P0.06/MISO), U2.7 (SDO)
/SPI_MOSI: U1.2 (P0.05/MOSI), U2.6 (SDI)
/SPI_SCK: U1.1 (P0.04/SCK), U2.5 (SCLK)
/TEMP_ALRT: U1.9 (P0.12), U3.3 (ALERT)
unnamed: AE1.1 (FEED), U1.16 (ANT)
unnamed: D1.1 (K), U2.1 (LED1_DRV)
unnamed: D2.1 (K), U2.2 (LED2_DRV)
unnamed: D3.1 (K), U2.3 (PD1_IN)
unnamed: C6.1, U1.11 (DCCH)
unnamed: C7.1, U1.14 (XC1), Y1.1
unnamed: C8.1, U1.15 (XC2), Y1.2
unnamed: L1.1, U5.6 (SW)
VBAT: BT1.1 (+), C3.1, C11.1, D1.2 (A), D2.2 (A), U2.11 (VLED), U5.5 (BAT)
VSYS: C4.1, L1.2, U1.12 (VDDH), U5.7 (SYS)

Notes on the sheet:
OPTICAL FRONT-END
LED anodes on VBAT; MAX86141 drivers sink the cathodes (0-124 mA, set in firmware)
MCU + BLE RADIO
Pull-ups 4.7k to +1V8, one I2C bus at 400 kHz
SENSORS
U3: ADD0 = GND -> address 0x48
U4: CS = SA0 = +1V8 -> I2C mode, address 0x19
DECOUPLING
One 100 nF / 1 uF next to each supply pin
CHARGER + BATTERY
SYS buck = 3.3 V (set over I2C) -> nRF52840 VDDH; REG0 makes +1V8

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
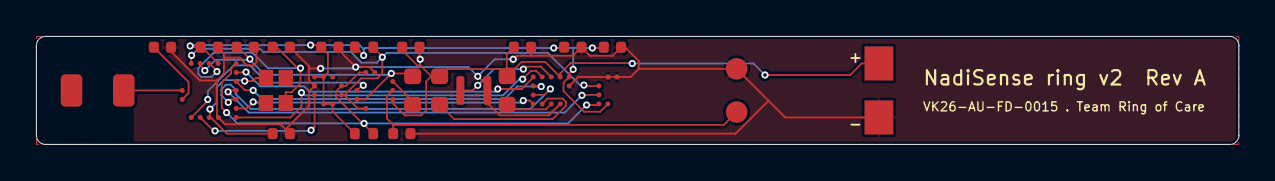
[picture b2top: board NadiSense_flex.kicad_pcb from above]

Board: 2 copper layers, 66.8 x 6.0 mm, 26 parts (0 on the bottom side), 23 nets.

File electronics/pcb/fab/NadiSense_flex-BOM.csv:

Qty,References,Value,Footprint
1,AE1,2450AT18A100,RF_Antenna:Johanson_2450AT18x100
1,BT1,Li-Po 3.7V 12mAh,NadiSense:NS_LiPo_Tabs
2,C11 C4,10uF,Capacitor_SMD:C_0402_1005Metric
3,C1 C3 C5,1uF,Capacitor_SMD:C_0402_1005Metric
1,C6,10nF,Capacitor_SMD:C_0402_1005Metric
2,C7 C8,12pF,Capacitor_SMD:C_0402_1005Metric
3,C10 C2 C9,100nF,Capacitor_SMD:C_0402_1005Metric
1,D1,Red 660 nm,LED_SMD:LED_0603_1608Metric
1,D2,IR 880 nm,LED_SMD:LED_0603_1608Metric
1,D3,Si PIN photodiode,NadiSense:NS_PD_2x2mm
1,J1,Pogo pads,NadiSense:NS_ChargePads_2x1.2mm
1,L1,2.2uH,Inductor_SMD:L_0603_1608Metric
2,R1 R2,4.7k,Resistor_SMD:R_0402_1005Metric
1,U1,nRF52840-QIAA,NadiSense:NS_U1_nRF52840
1,U2,MAX86141,NadiSense:NS_U2_MAX86141
1,U3,TMP117AIDRVR,NadiSense:NS_U3_TMP117
1,U4,LIS2DW12TR,NadiSense:NS_U4_LIS2DW12
1,U5,BQ25120AYFPR,NadiSense:NS_U5_BQ25120A
1,Y1,32MHz,NadiSense:NS_XTAL_2016
